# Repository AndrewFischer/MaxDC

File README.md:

# MaxDC
Unregulated Dual Linear Power Supply.

The 99.5x100mm Board fits in a Hammond 1455N1201 or 1202 case. The case is 20mm longer then the PCB which leaves room for connections.  
T1 is a 25VA Telema 7006xK. The 15VA 7005xK have the same foot print.

C9 and C10 must be rated for Class-Y line to ground use.  
Optional parts RS1, RS2, CS1 and CS2 form snubbers. See [snubber.pdf](Datasheets/snubber.pdf) in the Datasheets folder for details on selecting values.

<br>  
:exclamation: Danger of electric shock. 240Volts AC is present on this board. A suitable enclosure is required for safe operation.<br>
:warning: The files embodied in this repository are provided to you "as-is" and without warranty of any kind, express, implied or otherwise, including without limitation, any warranty of fitness for a particular purpose. See section 5 of the license.<br>
**This project is untested.**

### License
[cc-by-nc 4.0](LICENSE.md)

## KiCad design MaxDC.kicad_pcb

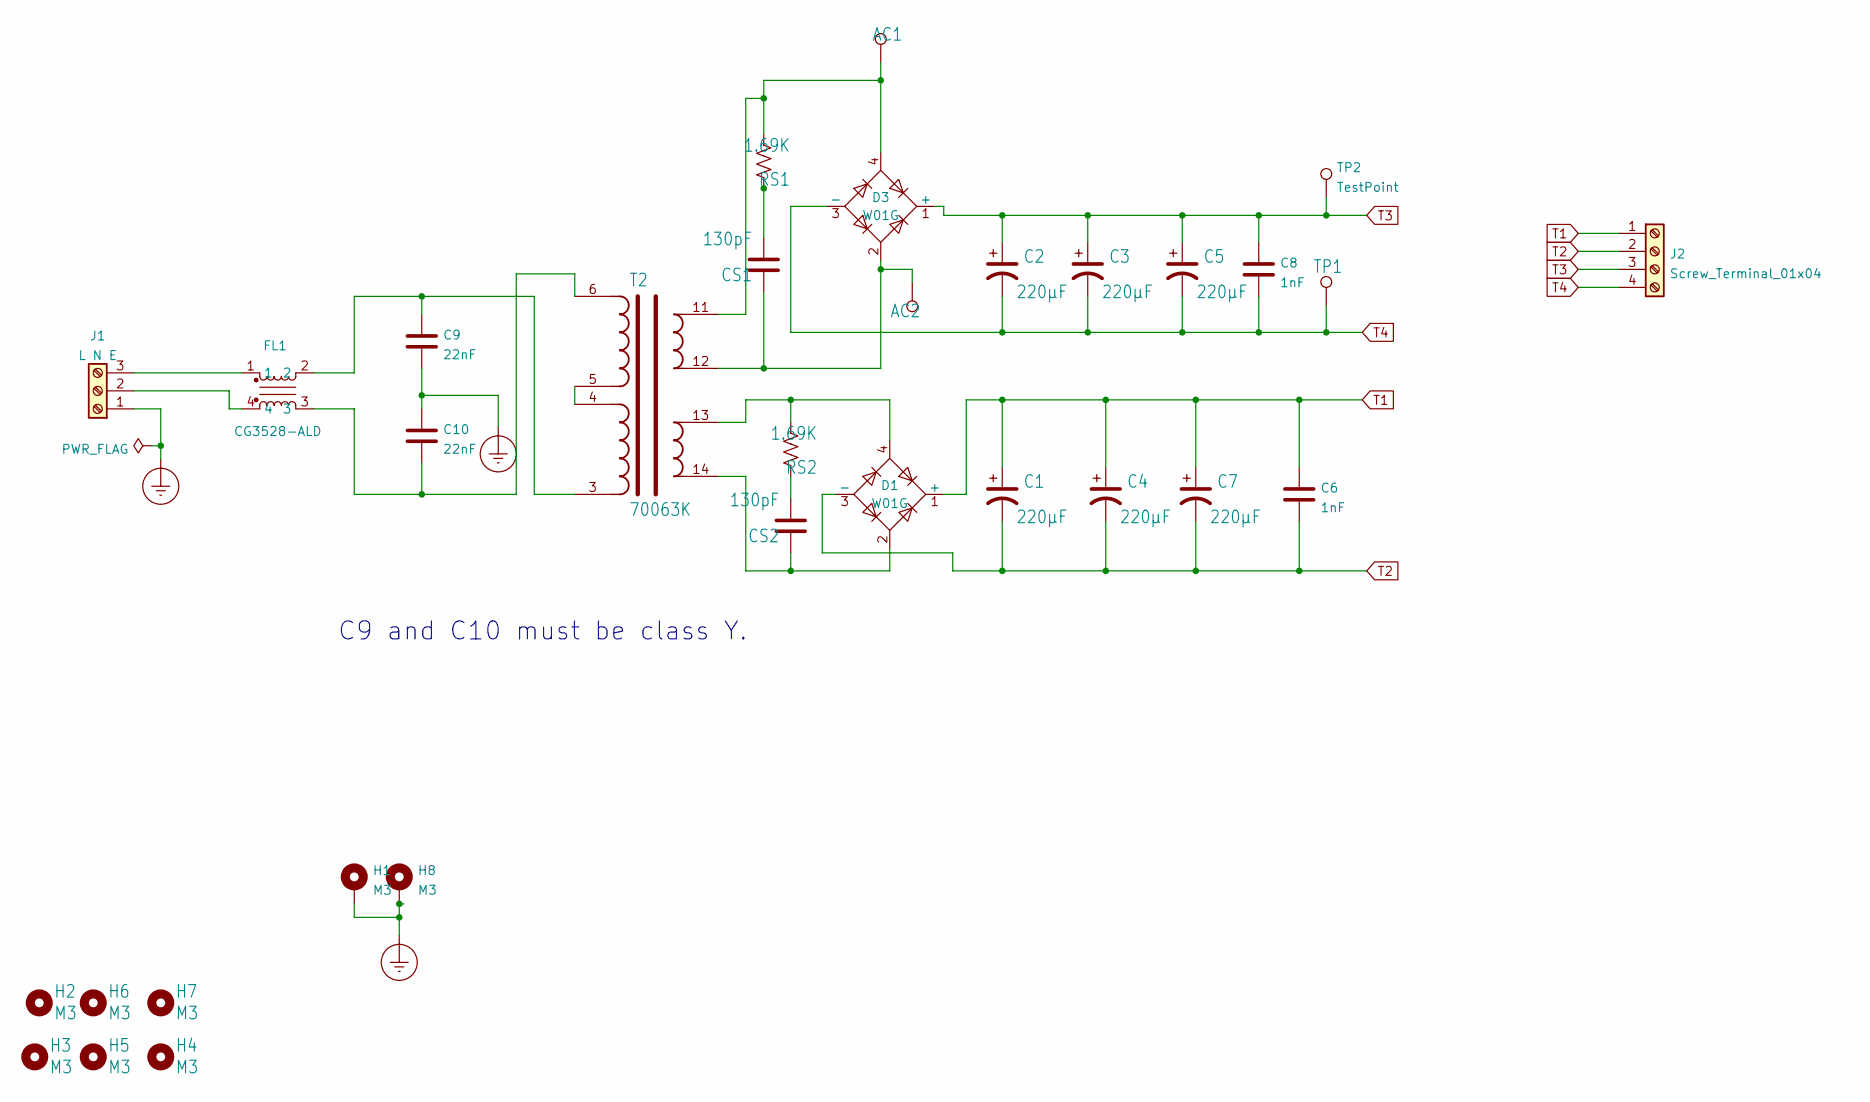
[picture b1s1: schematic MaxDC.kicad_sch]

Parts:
AC1, AC2: SE13; TestPoint_THTPad_3.0x3.0mm_Drill1.5mm
C1, C2, C3, C4, C5, C7: 220µF; CP_Radial_D10.0mm_P5.00mm; MPN UPW1H221MPD
C6, C8: 1nF; C_0805_2012Metric_Pad1.18x1.45mm_HandSolder; MPN CL21B102KBCNNNC; LCSC C46653
C9: 22nF; C_Rect_L18.0mm_W8.0mm_P15.00mm_FKS3_FKP3; MPN Kemet R413I222050M1M
C10: 22nF; C_Rect_L18.0mm_W8.0mm_P15.00mm_FKS3_FKP3; MPN R413I222050M1M
CS1, CS2: 130pF; C_0805_2012Metric_Pad1.18x1.45mm_HandSolder; MPN CC0805JRNPO9BN131; LCSC C520003
D1, D3: W01G; Diode_Bridge_Round_D9.8mm
FL1: CG3528-ALD; L_CoilCraft_CG3528AL
H1, H8: M3; MountingHole_3.2mm_M3_Pad
H2, H3, H4, H5, H6, H7: M3; MountingHole_3.2mm_M3
J1: L N E; TerminalBlock_Phoenix_MKDS-3-3-5.08_1x03_P5.08mm_Horizontal
J2: Screw_Terminal_01x04; TerminalBlock_Phoenix_MKDS-1,5-4-5.08_1x04_P5.08mm_Horizont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
RS1, RS2: 1.69K; R_0805_2012Metric_Pad1.20x1.40mm_HandSolder; MPN WR08X1691FTL; LCSC C170810
T2: 70063K; 70060K
TP1: SE13; TestPoint_THTPad_2.5x2.5mm_Drill1.2mm
TP2: TestPoint; TestPoint_THTPad_2.5x2.5mm_Drill1.2mm

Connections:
Earth_Protective: C9.2, C10.1, H1.1, H8.1, J1.1
unnamed: AC1.1, D3.4, RS1.2, T2.11
unnamed: AC2.1, CS1.1, D3.2, T2.12
unnamed: C9.1, FL1.2, T2.3
unnamed: C10.2, FL1.3, T2.6
unnamed: CS1.2, RS1.1
unnamed: CS2.1, D1.2, T2.14
unnamed: CS2.2, RS2.1
unnamed: D1.4, RS2.2, T2.13
unnamed: FL1.1, J1.3
unnamed: FL1.4, J1.2
unnamed: T2.4, T2.5
T1: C1.1, C4.1, C6.2, C7.1, D1.1 (+), J2.1
T2: C1.2, C4.2, C6.1, C7.2, D1.3 (-), J2.2
T3: C2.1, C3.1, C5.1, C8.2, D3.1 (+), J2.3, TP2.1
T4: C2.2, C3.2, C5.2, C8.1, D3.3 (-), J2.4, TP1.1

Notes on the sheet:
C9 and C10 must be class Y.

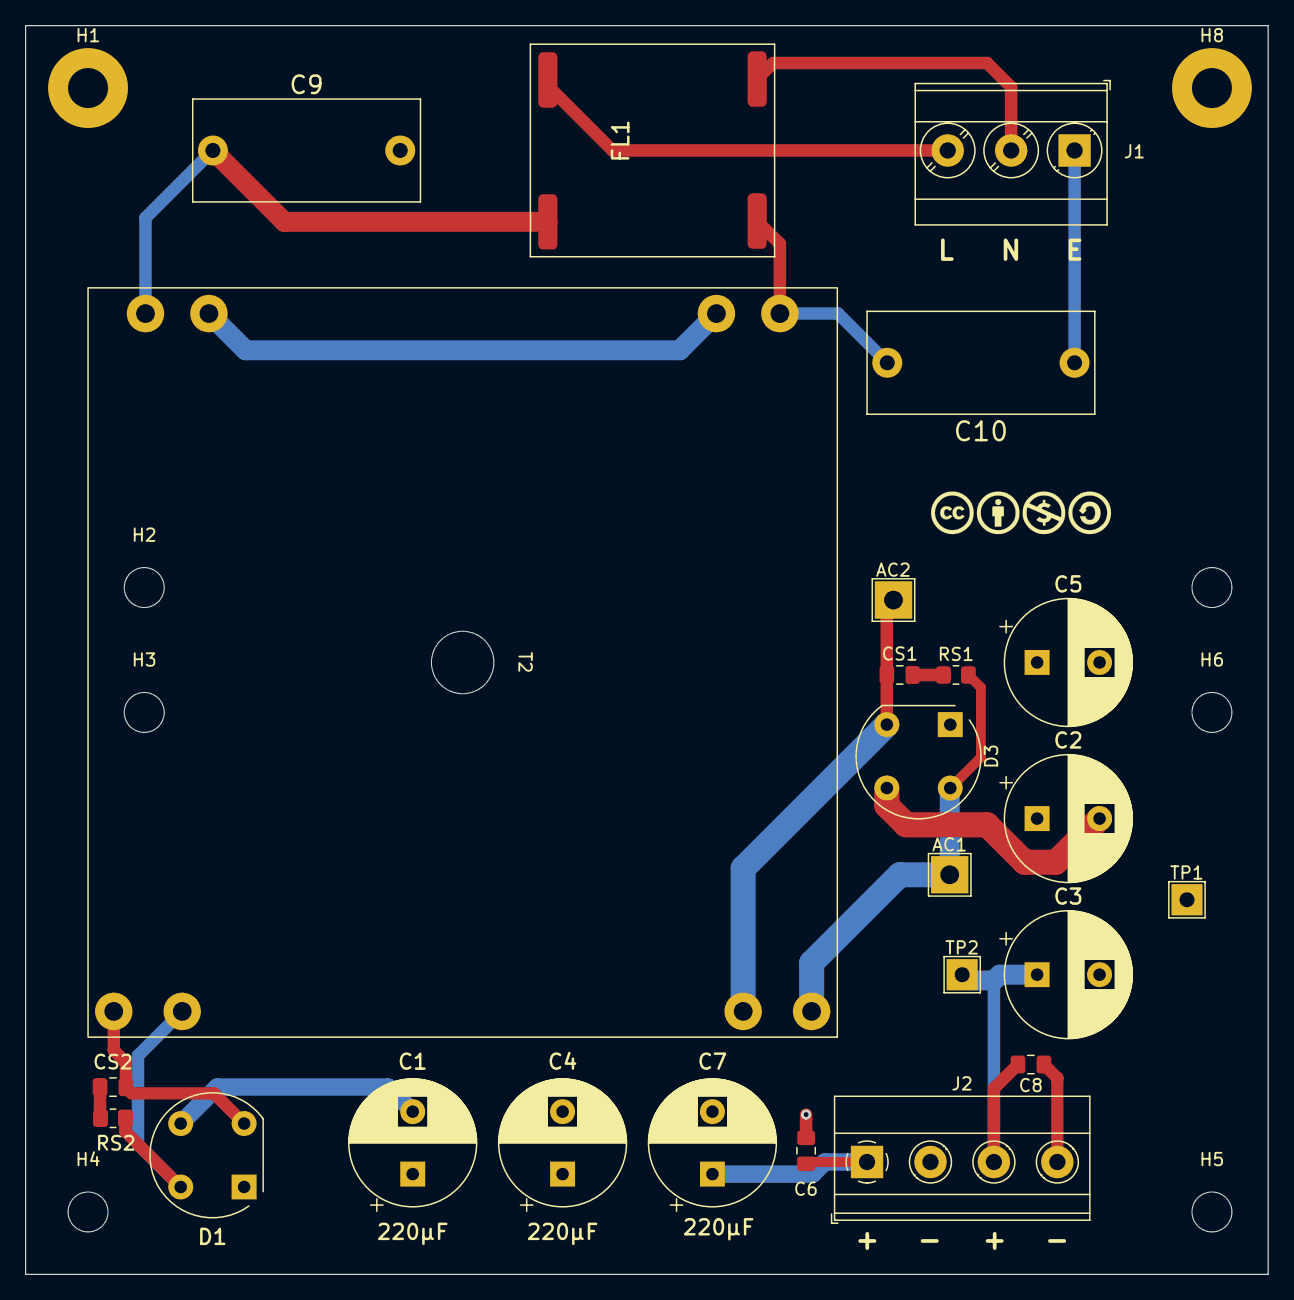
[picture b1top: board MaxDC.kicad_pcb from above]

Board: 2 copper layers, 99.5 x 100.0 mm, 32 parts (0 on the bottom side), 16 nets.

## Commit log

2023-01-23 Add files via upload
    Still using Eagle import for the transformer. Need to fix that.
2023-01-23 Add files via upload
    Fix symbol library path. CoilCraft symbol lib is now local to project.
    Respin PCB with CC By-NC logo and 240VAC warning
2023-01-24 Add files via upload
    Begin Changes for creepage. Reverse N and E input terminals.
2023-01-24 Add files via upload
    Adjust placement and spacing for 240VAC safety. Slots not needed.
2023-01-27 Add files via upload
    Rev 0.3 adjusts the board layout to fit inside a Hammond 1455 series enclosure. Move components and line voltage traces in from the edges of the PCB.
2023-01-28 Add files via upload
    28012023 Uploaded to JLCPCB
2023-01-30 Add files via upload
    Add Front Panel Design files. 1544N120x.fpd is a blank end panel for a Hammon 1455N case. MaxDCFront is the front panel.
2023-01-31 Add files via upload
    Correct 3.95mm corner radius.
2023-02-05 Add files via upload
    Uploaded to JLC. Branch ready to merge back to main.
    Move edge to the left and change width to 99.5mm. After checking a 100mm board in a 1455 case, I made this board .5mm wider. Move the edges to give the transformer a little more clearance.
    Moved the caps at the bottom of the board up 1mm. That is to give more clearance for output connectors. 5-way binding posts should clear, but this gives a little more leeway.
2023-03-17 Details about components
2023-03-18 Better 3D render of PCB
2023-03-18 Fix typos
2023-03-29 Better disclaimer and warning
2023-03-29 Move panels to folder
    Move the front panel design files to a folder. Better organisation

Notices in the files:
MaxDC.kicad_pcb:
License: Creative Commons CC BY-NC 4.0
creativecommons.org/licenses/by-nc/4.0
